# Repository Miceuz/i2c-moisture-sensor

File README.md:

# i2c-moisture-sensor

I2C based soil moisture sensor. A continuation of the [Chirp - plant watering alarm](https://github.com/Miceuz/PlantWateringAlarm) project. There is also an [RS485](https://github.com/Miceuz/rs485-moist-sensor) and an [analog](https://github.com/Miceuz/soil-moisture-sensor-analog) version available.

## I2C protocol
Available registers for reading and writing.

  Name | Register | R/W | Data length 
-------|----------|-----|-------------
GET_CAPACITANCE   | 0x00 | (r) | 2
SET_ADDRESS       | 0x01 | (w) | 1
GET_ADDRESS       | 0x02 | (r) | 1
MEASURE_LIGHT     | 0x03 | (w) | 0
GET_LIGHT         | 0x04 | (r) | 2
GET_TEMPERATURE   | 0x05 | (r) | 2
RESET             | 0x06 | (w) | 0
GET_VERSION       | 0x07 | (r) | 1
SLEEP             | 0x08 | (w) | 0
GET_BUSY          | 0x09 | (r) | 1

GET_BUSY returns 1 if any measurement is in progress, 0 otherwise.

## How to interpret the readings

16bit values are returned most significant byte first.

Both light and moisture sensors give relative values. Meaning, more moisture will give you higher reading, more light, lower reading. They are not calibrated to any particular si units - this is up to you.

Moisture is somewhat linear. I test all sensors before shipping and they give about 290 - 310 in free air at 5V supply.

Temperature is in Celsius, value is in tenths of degrees Celsius. I.e. value 252 would mean 25.2°C.

I didn't measure linearity of the light sensor, it gives 65535 in a dark room away form desk lamp. When it's dark, it takes longer to measure light, reading the light register while measurement is in progress will return the previous reading. Be aware, light sensor is pretty noisy.

Temperature is measured by the thermistor on the body of the sensor. Calculated absolute measurement accuracy is better than 2%. 

Note Upon reading the moisture or temperature value, a value form the previous read command is returned and the new measurement is started. If you do rare measurements and want to act instantly, do two consecutive readings to get the most up to date data. Also you can read GET_BUSY register via i2c - it will indicate when the measurement is done. Basically the process goes like this: read from GET_CAPACITANCE, discard results, then read from GET_BUSY until you get '0' as an answer, then read form GET_CAPACITANCE again - the returned value is the soil moisture NOW.

### Python library for Raspberry Pi

*NOTE: if you experience problems on Raspberry Pi 3, slow down I2C bus speed by adding this line to /boot/config.txt:*
**dtparam=i2c1_baudrate=30000**

[Göran Lundberg](https://github.com/ageir) has released a Python library for Raspberry Pi: [https://github.com/ageir/chirp-rpi](https://github.com/ageir/chirp-rpi)
It has a very comprehensive documentation and covers a lot of functionality.

Some features:
* Uses a trigger function to trigger all enabled sensors. User selectable.
* Get soil moisture in percent (requires calibration) or capacitance value.
* Several temperature scales to choose from. Celcius, Fahrenheit and Kelvin.
* Offset to calibrate the temperature sensor.
* Measurement timestamps for all on board sensors.
* Built in support for changing the I2C address of the sensor.
* Deep sleep mode to conserve power.
* Calibration tool for soil moisture.

### Raspberry Pi examples

This is interface class provided by Daniel Tamm and Jasper Wallace
```python
#!/usr/bin/python
# cannot use python3 because smbus not working there
# Modified script from https://github.com/JasperWallace/chirp-graphite/blob/master/chirp.py
# by DanielTamm

import smbus, time, sys

class Chirp:
	def __init__(self, bus=1, address=0x20):
		self.bus_num = bus
		self.bus = smbus.SMBus(bus)
		self.address = address
    
	def get_reg(self, reg):
		# read 2 bytes from register
		val = self.bus.read_word_data(self.address, reg)
		# return swapped bytes (they come in wrong order)
		return (val >> 8) + ((val & 0xFF) << 8)

	def reset(self):
		# To reset the sensor, write 6 to the device I2C address
		self.bus.write_byte(self.address, 6)

	def set_addr(self, new_addr):
		# To change the I2C address of the sensor, write a new address
		# (one byte [1..127]) to register 1; the new address will take effect after reset
		self.bus.write_byte_data(self.address, 1, new_addr)
		# second request is required since FW 0x26 to protect agains spurious address changes
		self.bus.write_byte_data(self.address, 1, new_addr)
		self.reset()
		self.address = new_addr

	def moist(self):
		# To read soil moisture, read 2 bytes from register 0
		return self.get_reg(0)

	def temp(self):
		# To read temperature, read 2 bytes from register 5
		return self.get_reg(5)

	def light(self):
		# To read light level, start measurement by writing 3 to the
		# device I2C address, wait for 3 seconds, read 2 bytes from register 4
		self.bus.write_byte(self.address, 3)
		time.sleep(1.5)
		return self.get_reg(4)

	def __repr__(self):
		return "<Chirp sensor on bus %d, addr %d>" % (self.bus_num, self.address)

if __name__ == "__main__":
	addr = 0x20
	if len(sys.argv) == 2:
		if sys.argv[1].startswith("0x"):
			addr = int(sys.argv[1], 16)
		else:
			addr = int(sys.argv[1])
	chirp = Chirp(1, addr)

	print chirp
	print "Moisture\tTemperature\tBrightness"
	while True:
		print "%d\t%d\t%d" % (chirp.moist(), chirp.temp(), chirp.light())
		time.sleep(1)
```

This is another RasPi example provided by user *krikk*
```python
#!/usr/bin/python

#https://github.com/adafruit/Adafruit-Raspberry-Pi-Python-Code/tree/master/Adafruit_I2C
from Adafruit_I2C import Adafruit_I2C
from time import sleep, strftime
from datetime import datetime
deviceAddr = 0x20

i2c = Adafruit_I2C( deviceAddr, -1, False )

#to change adress
#i2c.write8( 1, 0x22 )

#reset sensor, we need this otherwise i get inconsistent light reading in the dark...
i2c.write8( deviceAddr, 0x06 )
sleep(5)

i2c.write8(deviceAddr, 3)
sleep(3)
light = i2c.readU16(4, False)
temp = i2c.readS16(5, False)/float(10)
moisture = i2c.readU16(0, False)
print "Temperature\tMoisture\tBrightness"
print str(temp) + ":" + str(moisture) + ":" + str(light)
```

### Arduino library
Ingo Fischer has written an Arduino library for the sensor, it has a couple of ready made examples: https://github.com/Apollon77/I2CSoilMoistureSensor 

Below are old examples for bare-bones Arduino illustrating a basic I2C use.

### Arduino example
```arduino
#include <Wire.h>

void writeI2CRegister8bit(int addr, int value) {
  Wire.beginTransmission(addr);
  Wire.write(value);
  Wire.endTransmission();
}

unsigned int readI2CRegister16bit(int addr, int reg) {
  Wire.beginTransmission(addr);
  Wire.write(reg);
  Wire.endTransmission();
  delay(20);
  Wire.requestFrom(addr, 2);
  unsigned int t = Wire.read() << 8;
  t = t | Wire.read();
  return t;
}

void setup() {
  Wire.begin();
  Serial.begin(9600);
  writeI2CRegister8bit(0x20, 6); //reset
}

void loop() {
  Serial.print(readI2CRegister16bit(0x20, 0)); //read capacitance register
  Serial.print(", ");
  Serial.print(readI2CRegister16bit(0x20, 5)); //temperature register
  Serial.print(", ");
  writeI2CRegister8bit(0x20, 3); //request light measurement 
  Serial.println(readI2CRegister16bit(0x20, 4)); //read light register
}
```
### Note for ESP8266 based systems
In some cases the default ESP8266 Arduino I2C library has the clock stretching timeout set too low. If you experience intermittent communication, add this to your code:
```
Wire.setClockStretchLimit(2500)
```
### Micropython
Micropython library is available here: [https://github.com/scopelemanuele/pyChirpLib](https://github.com/scopelemanuele/pyChirpLib)

## Address change example
By default the sensor comes with 0x20 set as an address, this is an example on how to change address for indivitual sensor:
```arduino
#include <Wire.h>
 
void writeI2CRegister8bit(int addr, int reg, int value) {
  Wire.beginTransmission(addr);
  Wire.write(reg);
  Wire.write(value);
  Wire.endTransmission();
}
 
void writeI2CRegister8bit(int addr, int value) {
  Wire.beginTransmission(addr);
  Wire.write(value);
  Wire.endTransmission();
}
 
void setup() {
  Wire.begin();
  Serial.begin(9600);
                                       //talking to the default address 0x20
  writeI2CRegister8bit(0x20, 1, 0x21); //change address to 0x21
  writeI2CRegister8bit(0x20, 6);       //reset
  delay(1000);                         //give it some time to boot
}
 
/*loop scans I2C bus and displays foud addresses*/ 
void loop()
{
  byte error, address;
  int nDevices;
 
  Serial.println("Scanning...");
 
  nDevices = 0;
  for(address = 1; address < 127; address++ )
  {
    // The i2c_scanner uses the return value of
    // the Write.endTransmisstion to see if
    // a device did acknowledge to the address.
    Wire.beginTransmission(address);
    error = Wire.endTransmission();
 
    if (error == 0)
    {
      Serial.print("I2C device found at address 0x");
      if (address<16)
        Serial.print("0");
      Serial.print(address,HEX);
      Serial.println("  !");
 
      nDevices++;
    }
    else if (error==4)
    {
      Serial.print("Unknow error at address 0x");
      if (address<16)
        Serial.print("0");
      Serial.println(address,HEX);
    }    
  }
  if (nDevices == 0)
    Serial.println("No I2C devices found\n");
  else
    Serial.println("done\n");
 
  delay(5000);           // wait 5 seconds for next scan
}
```
### Particle Photon

There is a great [tutorial](ParticlePhoton-tutorial.md) by Miriam Cox for Particle Photon boards. Also there is a [library available](https://github.com/VintageGeek/I2CSoilMoistureSensor) by Mike.

## Links and mentions

* A [video from Growing Robot](https://www.youtube.com/watch?v=rB4vS7I0euA) about using the sensors with Raspberry Pi
* A [complete Open Source logging solution](https://git.jeelabs.org/jcw/zelkova) employing a batch of 40 sensors in Crete for tree monitoring
* [Chirp - Wemos - Azure bridge](https://github.com/korpiq/chirp-wemos-meter) ESP8266 based system that pushes sensor data to Azure cloud serivices.

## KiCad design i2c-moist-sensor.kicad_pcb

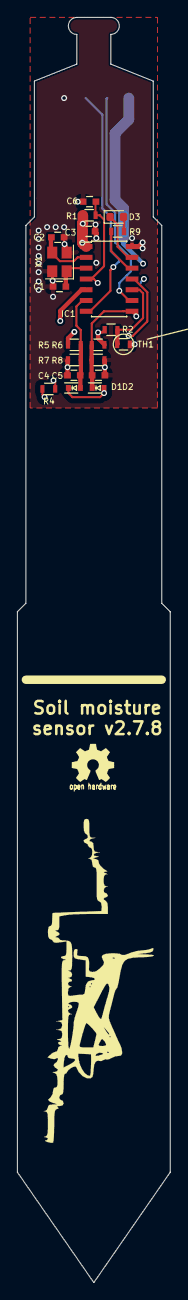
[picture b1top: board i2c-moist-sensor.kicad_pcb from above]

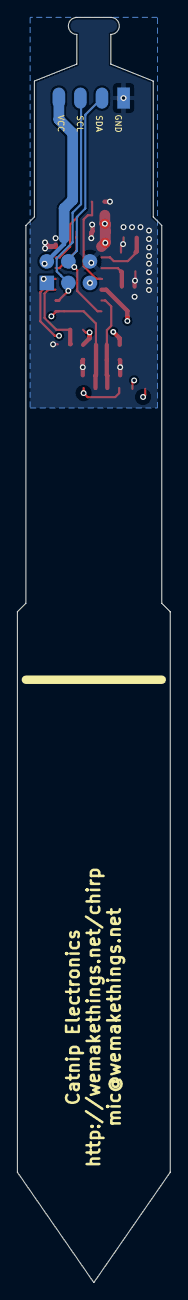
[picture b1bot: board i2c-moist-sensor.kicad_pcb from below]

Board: 4 copper layers, 18.0 x 149.0 mm, 22 parts (2 on the bottom side), 16 nets.

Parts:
C1: 33p; C_0603
C2: 33pp; C_0603
C3, C6: 1u; C_0603
C4, C5: 1n; C_0603
D1, D2: BAT54; SOD-523
D3: LED; LED_0603_1608Metric
IC1: ATTINY441-SSU; SOIC-14_3.9x8.7mm_Pitch1.27mm
P1: CONN_02X03; Pin_Header_Straight_2x03
P2: CONN_01X04; Pin_Header_Straight_1x04_Pitch2.54mm
R1: 10k; R_0603
R2: 10k 0.1%; R_0603
R4, R9: 330; R_0603
R5, R6, R7, R8: 1M; R_0603
TH1: NCP18XH103F03RB; R_0603
X1: 16MHz; Crystal_SMD_3225-4pin_3.2x2.5mm

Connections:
/EXCITATION: IC1.5, R4.2
/MISO/SENSE_HIGH: C5.1, D2.2, IC1.8, P1.1, R6.1, R8.2
/MOSI/SDA: IC1.7, P1.4, P2.2
/RESET: C6.1, IC1.4, P1.5, R1.1
/SCK/SCL: IC1.9, P1.3, P2.3
/SENSE_LOW: C4.1, D1.1, IC1.6, R5.1, R7.2
/SENSOR_TRACK: D1.2, D2.1, R4.1
/THERMISTOR: IC1.10, R2.2, TH1.1
GND: C1.2, C2.2, C3.2, C4.2, C5.2, C6.2, IC1.14, P1.6, P2.1, R7.1, R8.1, TH1.2, X1.2, X1.4
unnamed: C1.1, IC1.3, X1.1
unnamed: C2.1, IC1.2, X1.3
unnamed: D3.1, IC1.13
unnamed: D3.2, R9.1
unnamed: IC1.11, R2.1, R5.2, R6.2
unnamed: IC1.12, R9.2
VCC: C3.1, IC1.1, P1.2, P2.4, R1.2

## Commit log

2015-06-16 Initial
2015-06-16 Fix led name
2015-10-25 New eeschema libs are new. Move TH1 and R4 OUT of the soil. Minimize stray capacitance where it matters
2015-10-25 Stray edit
2015-10-26 Fix LED footprint according to the datasheet, add data for the bom to schematics
2015-10-26 Sleep to conserve the power
2015-10-26 Change xtal load cap value
2015-10-26 Put the new version to the pannel
2015-10-26 Add gerber
2015-10-26 Updated BOM
2015-10-27 Don't sleep automatically, instead add busy detection and explicit sleep call into protocol
2015-10-27 Mark temperature measurement also
2015-11-05 Add makefile
2015-11-13 add third party examples
2016-02-16 Enable BOD finally!
2016-02-16 Add standalone programmer/testrig code
2016-02-16 Add extended fuse with proper BOD settings to standalone programming/testing rig firmware
2016-02-23 Update README.md
    Fix the formatting of the first RPi example. Include header to the output of the second RPi example.
2016-03-16 A couple of small fixes - do some effort to avoid off readings after reset, also perform a proper capacitance calculation
2016-03-16 Add documentation about the new functions
2016-06-02 Add tutorial for Particle Photon
2016-06-02 Add tutorial for Particle Photon to README
2016-06-07 Remove unused variable
2017-03-27 Fix address validation so that it is compliant with NXP spec
2017-03-27 Adjust testing limits and delays
2017-03-27 Now we have a more up to date compiler and avr-libc, so no need for hacks. Also run ADC slower to possibly increase accuracy
2017-03-27 Remove sharp corners so that heatshrink lays nicer
2017-04-17 Fix README headings
2017-04-19 Changes for the next release - stronger vias connecting to the sensor pad, align caps for better coating convenience, use silkscreen as cover for problematic vias
2017-07-12 Add a 3d rendering of the sensor
2017-08-02 Power thermistor and moisture sensing circuitry from a pin rather than directly so lower the power consumption
2017-08-30 Add new Python library
2017-08-31 Change feature description forlLibrary by @ageir
2017-11-28 Firmware 2.4 - turn power on/off to resistive dividers
2017-12-08 Fix flops that prevent compiling on avr-gcc 7.2.0
2017-12-08 Add the latest gerbers
2017-12-08 Add heatshrink to BOM
2017-12-08 Shuffle stuff around
2017-12-08 Update revision number
2017-12-08 Unimportant stray changes to pro and rescue library files
2017-12-08 Add STEP file, not zip file
2017-12-08 Migrate to KiCad v.5
2017-12-24 Fix connections that were broken during v5 migration
2018-02-26 Don't receive TWI interrupts we are not interested in
2018-02-26 Sleep more and wait for the ADC conversion to finish as TWI interrupts can wake up the sensor from ADC sleep
2018-02-26 Bump FW version to 2.5
2018-04-27 Make wait for i2c byte timeout to avoid hanging. The new address change order - you have to issue the address change command two times for it to take effect. Bump software version to 2.6
2018-07-02 removed via's in earth
2018-07-02 4 layers, B.Cu -> In2.Cu
2018-07-03 In1.Cu - sensing pad
2018-07-03 add 1mm, F.Cu GND -> In1.Cu
2018-07-03 added gerbers for four layer pcb
2018-07-05 fixed unconnected
2018-07-06 C2||C6
2018-07-14 new header, connected SENSE-HIGH, RESET, GND
2018-07-20 new header
2018-07-20 changed crystal to SMD 3225
2018-07-20 generated new gerbers
2018-07-24 created and added 3D models, generated STEP file
2018-07-24 Move stuff around, shorten traces to crystal, fix silkscreen, add cable connector pads, send files for manufacturing
2018-10-02 Fixed Typo
2018-12-05 Change shape of the board to accomodate narrower heatshrink, recover schematics from kicad version rescue hell
2018-12-30 Add picture and 3d model of the new shape of the sensor
2018-12-30 Add FAQ work in progress
2018-12-30 Update FAQ.md
    Add more FAQ entries
2018-12-30 Add connector illustration
2019-02-19 add azure bridge description
2019-03-03 Update README.md
    Close #14 fix broken link
2019-10-08 New kicad library order
2019-10-08 Chase kicad format updates, add 3d step file of the sensor
2019-10-08 add 3dmodels
2019-10-08 One more kicad kiss
2019-12-23 Add Qwiic connectors
2019-12-24 Add Qwiic logo above connector on front of PCB
2020-01-28 Add schematics PDF
2020-07-22 Add calibration document
2020-08-03 Add silkscreen for temp sensor
2020-10-04 Gerbers are generated, remove them
2020-10-04 Add some random pics
2020-10-04 Ignore new style kicad backups
2020-10-04 Remove manufacturing files as they are generated
2023-02-25 Update README.md
    Add data format and value interpretation description. Fix #40
